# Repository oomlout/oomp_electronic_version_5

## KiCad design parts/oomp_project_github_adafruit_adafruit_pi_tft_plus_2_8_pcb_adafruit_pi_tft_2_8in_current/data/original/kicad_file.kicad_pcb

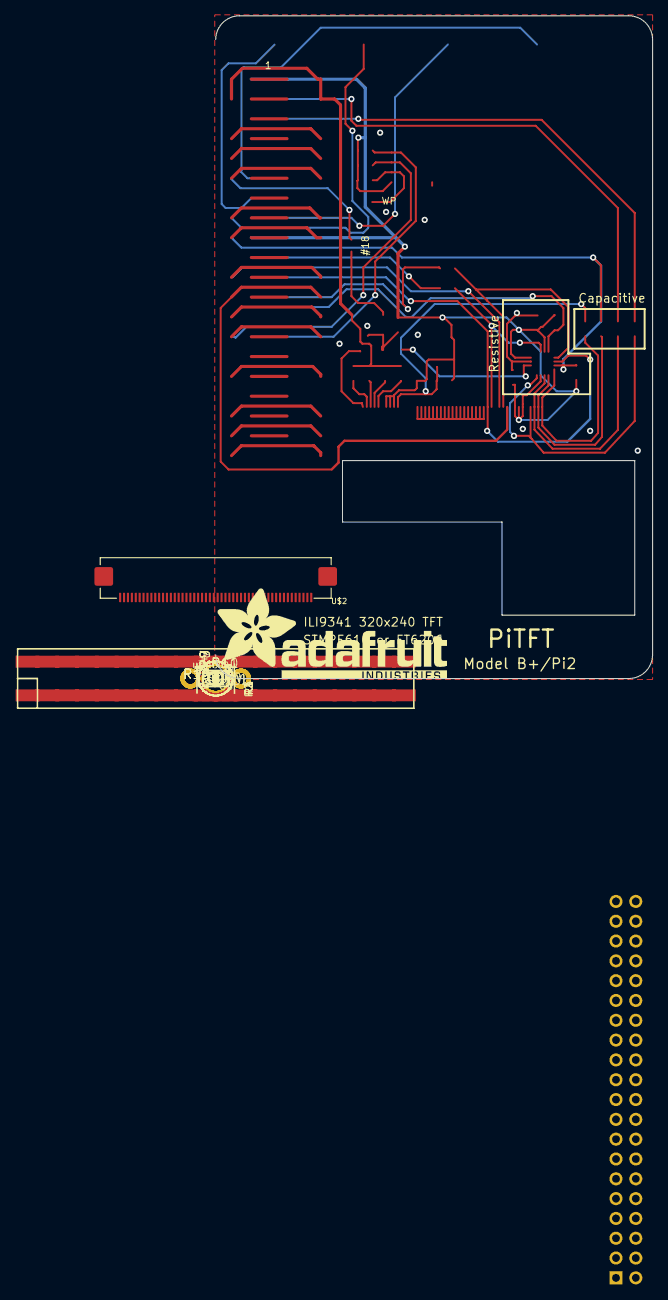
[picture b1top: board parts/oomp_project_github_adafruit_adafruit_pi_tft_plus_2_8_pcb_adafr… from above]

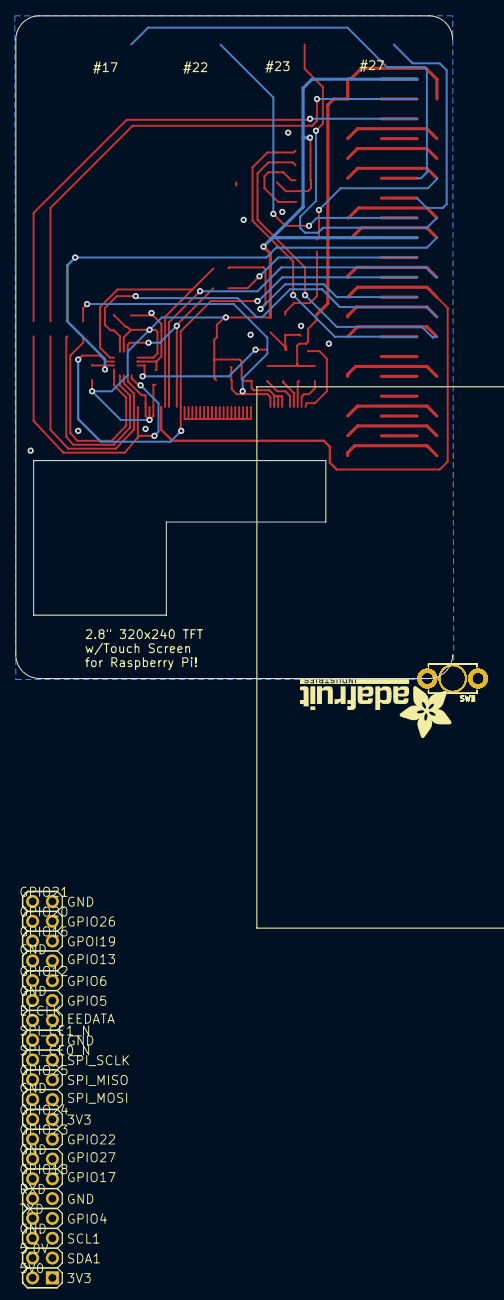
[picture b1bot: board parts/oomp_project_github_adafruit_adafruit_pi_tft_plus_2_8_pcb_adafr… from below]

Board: 16 copper layers, 56.0 x 85.0 mm, 48 parts (7 on the bottom side), 48 nets.

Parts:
C1, C5: 10uF; 0805-NO
C2, C3, C4: 0.1uF; 0805-NO
D1, D2: 1N4148; SOD-323
IC5: APX803; SOT23
JP3: 2X20_SMT_MALE
Q2: BSS138; SOT23-WIDE
R1, R2, R3, R4: 100; 0805-NO
R6, R7: 10K; 0805-NO
R8: DNP; 0805-NO
R9, R12, R13, R14: 3.9K; 0805-NO
R10, R11: 22; 0805-NO
R15, R16, R17, R18: 0; 0805-NO
RPI1: RASPBERRYPI_BPLUS_SHIELD_NODIM
SW1, SW2, SW3, SW4: TACT_PANA-EVQ
U1: CAT24C32; SOIC8_150MIL
U2: STMPE811; QFN16_3MM
U$2: DISP_LCD_240X320_50PIN_2.8IN; TFT_2.83IN_240X320_50PIN
U$3, U$15, U$16, U$17, U$40: MOUNTINGHOLE3.0THIN; MOUNTINGHOLE_3.0_PLATEDTHIN
U$10, U$11, U$18: FIDUCIAL""; FIDUCIAL_1MM
U$12: PCBFEAT-REV-040
U$23: ADAFRUIT_TEXT_20MM
U$42: ADAFRUIT_TEXT_30MM
WPJ0, WPJ1: SOLDERJUMPER_CLOSEDWIRE

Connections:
3.3V: C1.1, C2.1, C3.1, C4.1, IC5.3, JP3.1, JP3.17, R6.2, R7.2, R8.1, R9.2, R12.2, R13.2, R14.2, RPI1.1, RPI1.17, U1.8, U2.6, U2.9, U2.14, U$2.7, U$2.8, U$2.9, U$2.40, U$2.41, U$2.42
+5V: C5.1, JP3.2, JP3.4, R1.1, R2.1, R3.1, R4.1, RPI1.2, RPI1.4
EECLK: JP3.28, R14.1, RPI1.28, U1.6
EEDATA: JP3.27, R13.1, RPI1.27, U1.5
GND: C1.2, C2.2, C3.2, C4.2, C5.2, IC5.1, JP3.6, JP3.9, JP3.14, JP3.20, JP3.25, JP3.30, JP3.34, JP3.39, Q2.2, RPI1.6, RPI1.9, RPI1.14, RPI1.20, RPI1.25, RPI1.30, RPI1.34, RPI1.39, SW1.P$2, SW2.P$2, SW3.P$2, SW4.P$2, U1.1, U1.2, U1.3, U1.4, U2.10, U$2.6, U$2.43, U$2.48, U$2.49, U$2.50, WPJ0.1
GPIO4: JP3.7, RPI1.7
GPIO5: JP3.29, RPI1.29
GPIO6: JP3.31, RPI1.31
GPIO12: JP3.32, RPI1.32
GPIO13: JP3.33, RPI1.33
GPIO16: JP3.36, RPI1.36
GPIO17: JP3.11, RPI1.11, SW3.P$1
GPIO18: JP3.12, RPI1.12, WPJ1.1
GPIO19: JP3.35, RPI1.35
GPIO20: JP3.38, RPI1.38
GPIO21: JP3.40, RPI1.40
GPIO22: JP3.15, RPI1.15, SW1.P$1
GPIO23: JP3.16, RPI1.16, SW4.P$1
GPIO26: JP3.37, RPI1.37
GPIO27: JP3.13, RPI1.13, SW2.P$1
MISO: JP3.21, RPI1.21, U2.3, U$2.33
MOSI: R11.2, U2.7, U$2.34
MOSI_3V: JP3.19, R11.1, RPI1.19
unnamed: Q2.3, U$2.1
unnamed: R1.2, U$2.2
unnamed: R2.2, U$2.3
unnamed: R3.2, U$2.4
unnamed: D1.C, U2.11
unnamed: D2.C, WPJ1.2
unnamed: U$2.15, U$2.16, U$2.17, U$2.18, U$2.19, U$2.20, U$2.21, U$2.22, U$2.23, U$2.24, U$2.25, U$2.26, U$2.27, U$2.28, U$2.29, U$2.30, U$2.31, U$2.32
unnamed: R4.2, U$2.5
unnamed: R12.1, U1.7, WPJ0.2
unnamed: D1.A, D2.A, Q2.1, R9.1
RT_CS_3V: JP3.26, R7.1, RPI1.26, U2.5
RT_INT: JP3.18, R8.2, R18.2, RPI1.18, U2.2
RXD: JP3.10, RPI1.10
SCL: JP3.5, R17.2, RPI1.5
SCLK: R10.2, U2.4, U$2.37
SCLK_3V: JP3.23, R10.1, RPI1.23
SDA: JP3.3, R16.2, RPI1.3
TFT_CS_3V: JP3.24, RPI1.24, U$2.38
TFT_DC_3V: JP3.22, RPI1.22, U$2.36
TFT_RST: IC5.2, R6.1, R15.2, U$2.10
TXD: JP3.8, RPI1.8
XL_CTPIRQ: R18.1, U2.16, U$2.46
XR_CTPSCL: R17.1, U2.13, U$2.44
YD_CTPSDA: R16.1, U2.15, U$2.45
YU_CTPRST: R15.1, U2.1, U$2.47

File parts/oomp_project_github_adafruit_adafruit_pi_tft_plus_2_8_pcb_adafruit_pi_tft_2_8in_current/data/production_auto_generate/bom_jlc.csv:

Comment,Designator,Footprint,LCSC Part #
,JP3,Adafruit PiTFT+ 2.8in-import-fps:2X20_SMT_MALE,
,U$23,Adafruit PiTFT+ 2.8in-import-fps:ADAFRUIT_TEXT_20MM,
,U$42,Adafruit PiTFT+ 2.8in-import-fps:ADAFRUIT_TEXT_30MM,
,U$12,Adafruit PiTFT+ 2.8in-import-fps:PCBFEAT-REV-040,
,"WPJ0,WPJ1",Adafruit PiTFT+ 2.8in-import-fps:SOLDERJUMPER_CLOSEDWIRE,
0,"R15,R16,R17,R18",Adafruit PiTFT+ 2.8in-import-fps:0805-NO,C2907288
0.1uF,"C2,C3,C4",Adafruit PiTFT+ 2.8in-import-fps:0805-NO,
100,"R1,R2,R3,R4",Adafruit PiTFT+ 2.8in-import-fps:0805-NO,C17408
10K,"R6,R7",Adafruit PiTFT+ 2.8in-import-fps:0805-NO,C17414
10uF,"C1,C5",Adafruit PiTFT+ 2.8in-import-fps:0805-NO,
1N4148,"D1,D2",Adafruit PiTFT+ 2.8in-import-fps:SOD-323,
22,"R10,R11",Adafruit PiTFT+ 2.8in-import-fps:0805-NO,C2907310
3.9K,"R9,R12,R13,R14",Adafruit PiTFT+ 2.8in-import-fps:0805-NO,C2907252
APX803,IC5,Adafruit PiTFT+ 2.8in-import-fps:SOT23,
BSS138,Q2,Adafruit PiTFT+ 2.8in-import-fps:SOT23-WIDE,C52895
CAT24C32,U1,Adafruit PiTFT+ 2.8in-import-fps:SOIC8_150MIL,
DISP_LCD_240X320_50PIN_2.8IN,U$2,Adafruit PiTFT+ 2.8in-import-fps:TFT_2.83IN_240X320_50PIN,
DNP,R8,Adafruit PiTFT+ 2.8in-import-fps:0805-NO,
"FIDUCIAL""""","U$10,U$11,U$18",Adafruit PiTFT+ 2.8in-import-fps:FIDUCIAL_1MM,
RASPBERRYPI_BPLUS_SHIELD_NODIM,RPI1,Adafruit PiTFT+ 2.8in-import-fps:RASPBERRYPI_BPLUS_SHIELD_NODIM,
STMPE811,U2,Adafruit PiTFT+ 2.8in-import-fps:QFN16_3MM,

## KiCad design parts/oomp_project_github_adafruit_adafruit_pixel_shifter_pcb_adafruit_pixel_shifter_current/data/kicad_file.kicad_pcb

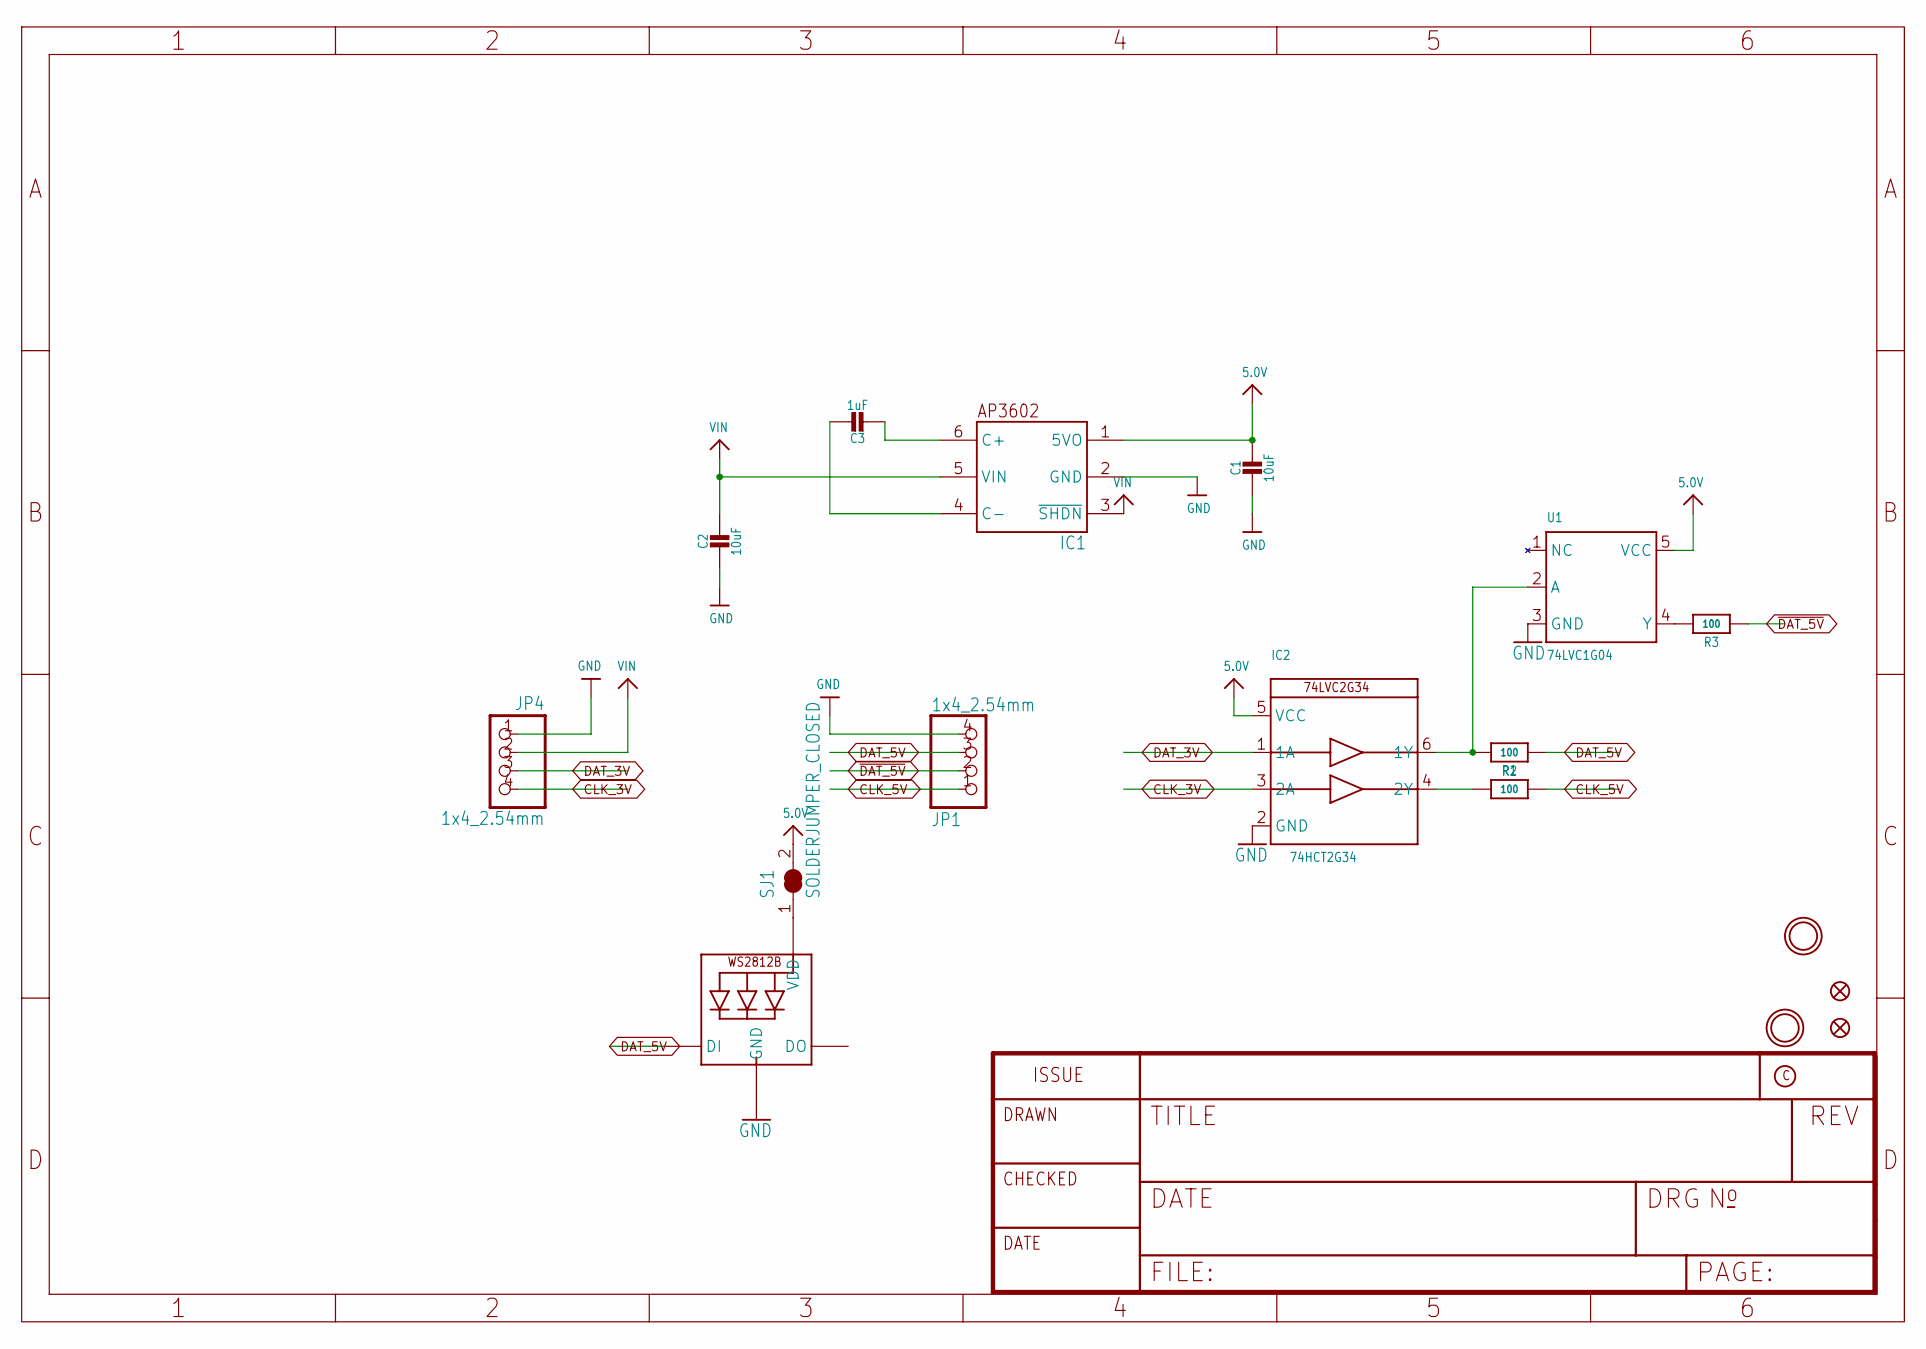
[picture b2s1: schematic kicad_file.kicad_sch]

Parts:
C1, C2: 10uF; 0805-NO
C3: 1uF; 0603-NO_WIDE
FID1, FID2: FIDUCIAL_0.5MM
IC1: AP3602; SOT23-6
IC2: 74HCT2G34; SC70-6L
JP1, JP4: 1x4_2.54mm; 1X04_2.54MMTERMINAL
LED1: WS2812B_SK6805_1515; SK6805_1515; LCSC C2890035
R1, R2, R3: 100; _0402NO
SJ1: SOLDERJUMPER_CLOSED; SOLDERJUMPER_CLOSEDWIRE
U1: 74LVC1G04; SC70-5
U$6, U$9: MOUNTINGHOLE2.5; MOUNTINGHOLE_2.5_PLATED

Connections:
5.0V: C1.1, IC1.1 (5VO), IC2.5 (VCC), SJ1.2, U1.5 (VCC)
CLK_3V: IC2.3 (2A), JP4.4
CLK_5V: JP1.1, R1.2
DAT_3V: IC2.1 (1A), JP4.3
DAT_5V: JP1.3, LED1.1 (DI), R2.2
GND: C1.2, C2.2, IC1.2 (GND), IC2.2 (GND), JP1.4, JP4.1, LED1.4 (GND), U1.3 (GND)
unnamed: C3.2, IC1.6 (C+)
unnamed: C3.1, IC1.4 (C-)
unnamed: IC2.4 (2Y), R1.1
unnamed: R3.1, U1.4 (Y)
unnamed: IC2.6 (1Y), R2.1, U1.2 (A)
unnamed: LED1.2 (VDD), SJ1.1
VIN: C2.1, IC1.3 (~SHDN), IC1.5 (VIN), JP4.2
~DAT_5V: JP1.2, R3.2

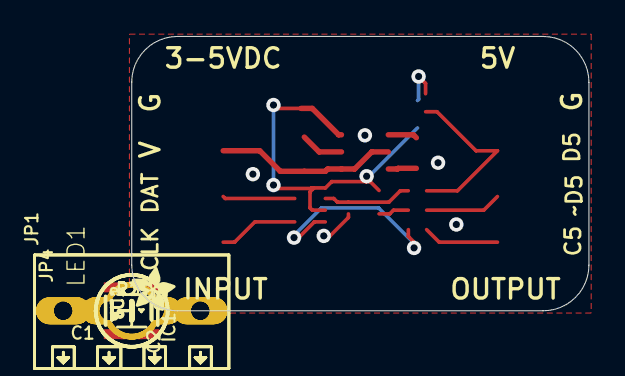
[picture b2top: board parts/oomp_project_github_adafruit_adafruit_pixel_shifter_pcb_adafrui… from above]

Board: 2 copper layers, 25.4 x 15.2 mm, 18 parts (1 on the bottom side), 14 nets.

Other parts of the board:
U$11: ADAFRUIT_2.5MM

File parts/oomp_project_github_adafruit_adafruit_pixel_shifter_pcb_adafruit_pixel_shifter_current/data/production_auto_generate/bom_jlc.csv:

Comment,Designator,Footprint,LCSC Part #
,U$11,Adafruit Pixel Shifter-import-fps:ADAFRUIT_2.5MM,
100,"R1,R2,R3",Adafruit Pixel Shifter-import-fps:_0402NO,C2906860
10uF,"C1,C2",Adafruit Pixel Shifter-import-fps:0805-NO,
1uF,C3,Adafruit Pixel Shifter-import-fps:0603-NO_WIDE,C5673
1x4_2.54mm,"JP1,JP4",Adafruit Pixel Shifter-import-fps:1X04_2.54MMTERMINAL,C42431795
74HCT2G34,IC2,Adafruit Pixel Shifter-import-fps:SC70-6L,
74LVC1G04,U1,Adafruit Pixel Shifter-import-fps:SC70-5,
AP3602,IC1,Adafruit Pixel Shifter-import-fps:SOT23-6,
WS2812B_SK6805_1515,LED1,Adafruit Pixel Shifter-import-fps:SK6805_1515,

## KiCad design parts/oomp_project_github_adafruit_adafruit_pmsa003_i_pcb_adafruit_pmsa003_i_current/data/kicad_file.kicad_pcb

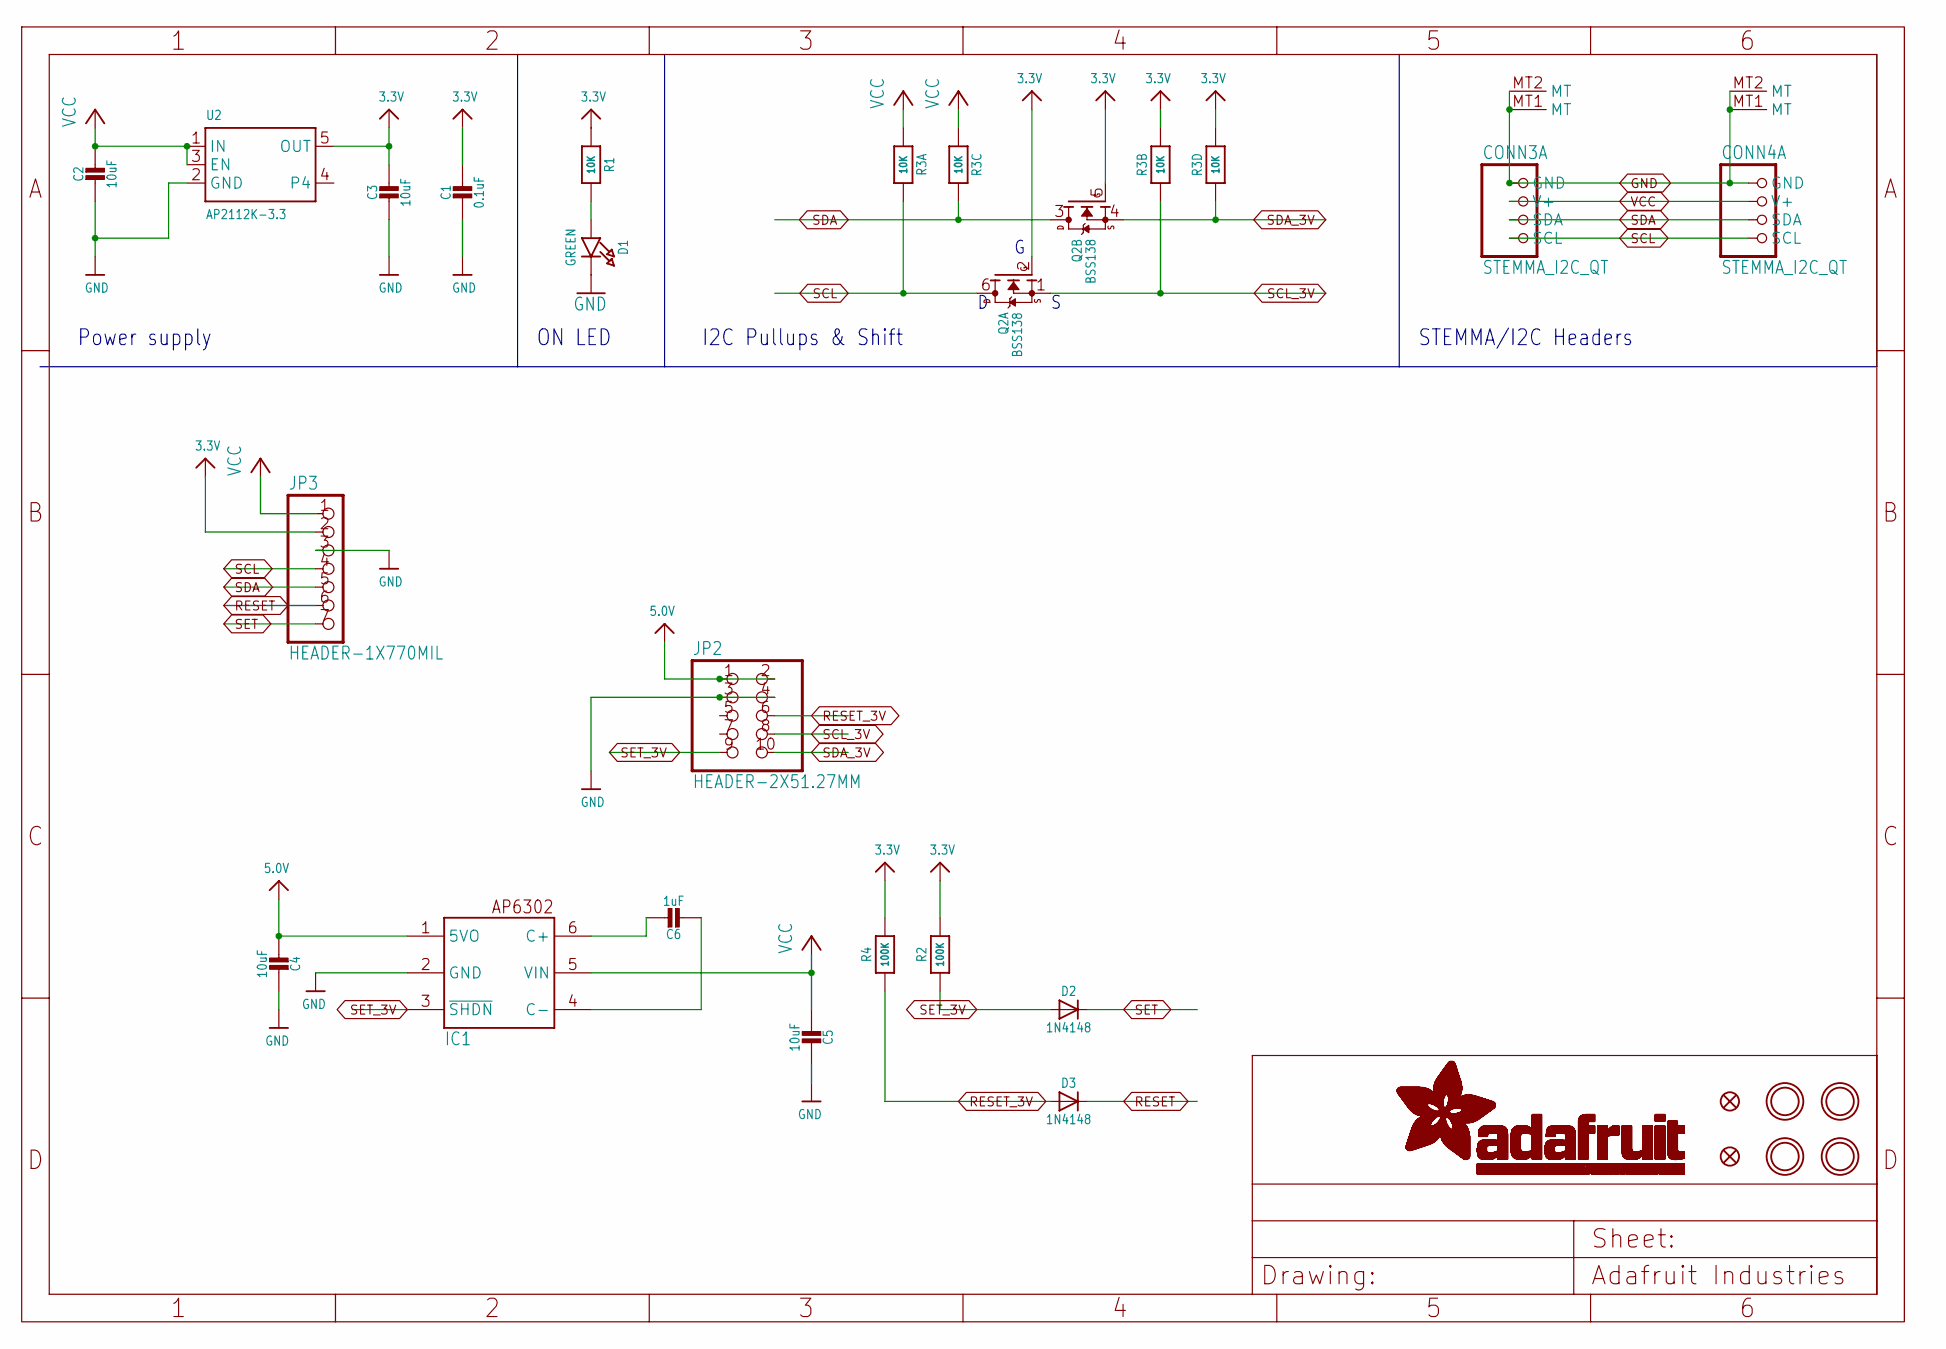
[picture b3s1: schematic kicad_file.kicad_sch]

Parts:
C1: 0.1uF; 0603-NO
C2, C3, C4: 10uF; 0805-NO
C5: 10uF; 0805_10MGAP
C6: 1uF; 0805-NO
CONN3, CONN4: STEMMA_I2C_QT; JST_SH4
D1: GREEN; CHIPLED_0603_NOOUTLINE
D2, D3: 1N4148; SOD-323
FID3, FID4: FIDUCIAL_1MM
IC1: AP3602/RT9361; SOT23-6
JP2: HEADER-2X51.27MM; 2X05_1.27MM_SMT
JP3: HEADER-1X770MIL; 1X07_ROUND_70
Q2: BSS138; SOT363
R1: 10K; 0603-NO
R2, R4: 100K; 0603-NO
R3: 10K; RESPACK_4X0603
U2: AP2112K-3.3; SOT23-5
U$1, U$17, U$19, U$21: MOUNTINGHOLE2.5; MOUNTINGHOLE_2.5_PLATED

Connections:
3.3V: C1.1, C3.1, JP3.2, Q2.2 (G), Q2.5 (G), R1.1, R2.1, R3.2 (1), R3.4 (1), R4.1, U2.5 (OUT)
5.0V: C4.1, IC1.1 (5VO), JP2.1, JP2.2
GND: C1.2, C2.2, C3.2, C4.2, C5.2, CONN3.1 (GND), CONN3.MT1 (MT), CONN3.MT2 (MT), CONN4.1 (GND), CONN4.MT1 (MT), CONN4.MT2 (MT), D1.C, IC1.2 (GND), JP2.3, JP2.4, JP3.3, U2.2 (GND)
unnamed: D1.A, R1.2
unnamed: C6.2, IC1.6 (C+)
unnamed: C6.1, IC1.4 (C-)
RESET: D3.C, JP3.6
RESET_3V: D3.A, JP2.6, R4.2
SCL: CONN3.4 (SCL), CONN4.4 (SCL), JP3.4, Q2.6 (D), R3.8 (2)
SCL_3V: JP2.8, Q2.1 (S), R3.7 (2)
SDA: CONN3.3 (SDA), CONN4.3 (SDA), JP3.5, Q2.3 (D), R3.6 (2)
SDA_3V: JP2.10, Q2.4 (S), R3.5 (2)
SET: D2.C, JP3.7
SET_3V: D2.A, IC1.3 (~SHDN), JP2.9, R2.2
VCC: C2.1, C5.1, CONN3.2 (V+), CONN4.2 (V+), IC1.5 (VIN), JP3.1, R3.1, R3.3 (1), U2.1 (IN), U2.3 (EN)

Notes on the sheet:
I2C Pullups & Shift
STEMMA/I2C Headers
ON LED
Power supply

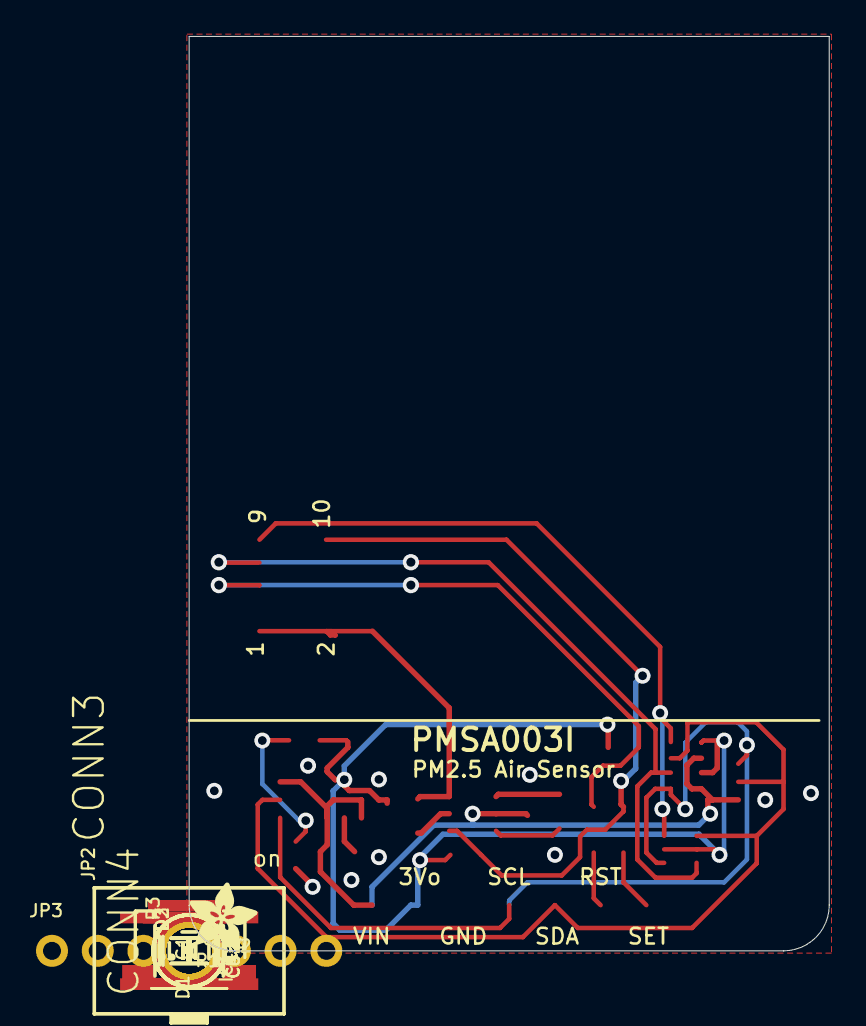
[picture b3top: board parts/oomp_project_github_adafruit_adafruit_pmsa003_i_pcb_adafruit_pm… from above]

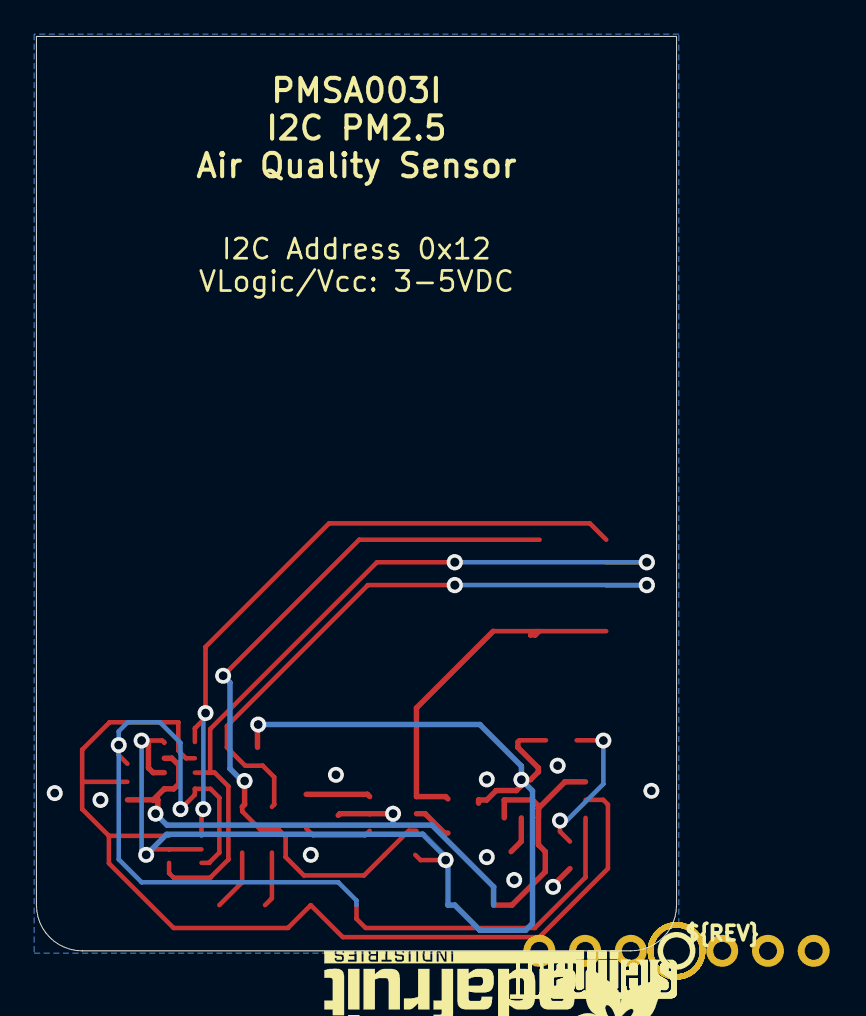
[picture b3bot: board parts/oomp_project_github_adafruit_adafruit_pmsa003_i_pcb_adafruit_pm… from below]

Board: 2 copper layers, 35.6 x 50.8 mm, 31 parts (4 on the bottom side), 15 nets.

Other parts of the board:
U$22: ADAFRUIT_3.5MM
U$25: PCBFEAT-REV-040
U$28: ADAFRUIT_TEXT_20MM
U$30, U$31: STEMMAQT

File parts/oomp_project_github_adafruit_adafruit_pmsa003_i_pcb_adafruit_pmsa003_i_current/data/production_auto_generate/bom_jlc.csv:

Comment,Designator,Footprint,LCSC Part #
,JP3,Adafruit PMSA003I-import-fps:1X07_ROUND_70,C7501585
,JP2,Adafruit PMSA003I-import-fps:2X05_1.27MM_SMT,
,U$22,Adafruit PMSA003I-import-fps:ADAFRUIT_3.5MM,
,U$28,Adafruit PMSA003I-import-fps:ADAFRUIT_TEXT_20MM,
,U$25,Adafruit PMSA003I-import-fps:PCBFEAT-REV-040,
,"U$30,U$31",Adafruit PMSA003I-import-fps:STEMMAQT,
0.1uF,C1,Adafruit PMSA003I-import-fps:0603-NO,C14663
100K,"R2,R4",Adafruit PMSA003I-import-fps:0603-NO,C25803
10K,R1,Adafruit PMSA003I-import-fps:0603-NO,C98220
10K,R3,Adafruit PMSA003I-import-fps:RESPACK_4X0603,C98220
10uF,"C2,C3,C4",Adafruit PMSA003I-import-fps:0805-NO,
10uF,C5,Adafruit PMSA003I-import-fps:0805_10MGAP,
1N4148,"D2,D3",Adafruit PMSA003I-import-fps:SOD-323,
1uF,C6,Adafruit PMSA003I-import-fps:0805-NO,
AP2112K-3.3,U2,Adafruit PMSA003I-import-fps:SOT23-5,
AP3602/RT9361,IC1,Adafruit PMSA003I-import-fps:SOT23-6,
BSS138,Q2,Adafruit PMSA003I-import-fps:SOT363,
GREEN,D1,Adafruit PMSA003I-import-fps:CHIPLED_0603_NOOUTLINE,
STEMMA_I2C_QT,"CONN3,CONN4",Adafruit PMSA003I-import-fps:JST_SH4,C160404

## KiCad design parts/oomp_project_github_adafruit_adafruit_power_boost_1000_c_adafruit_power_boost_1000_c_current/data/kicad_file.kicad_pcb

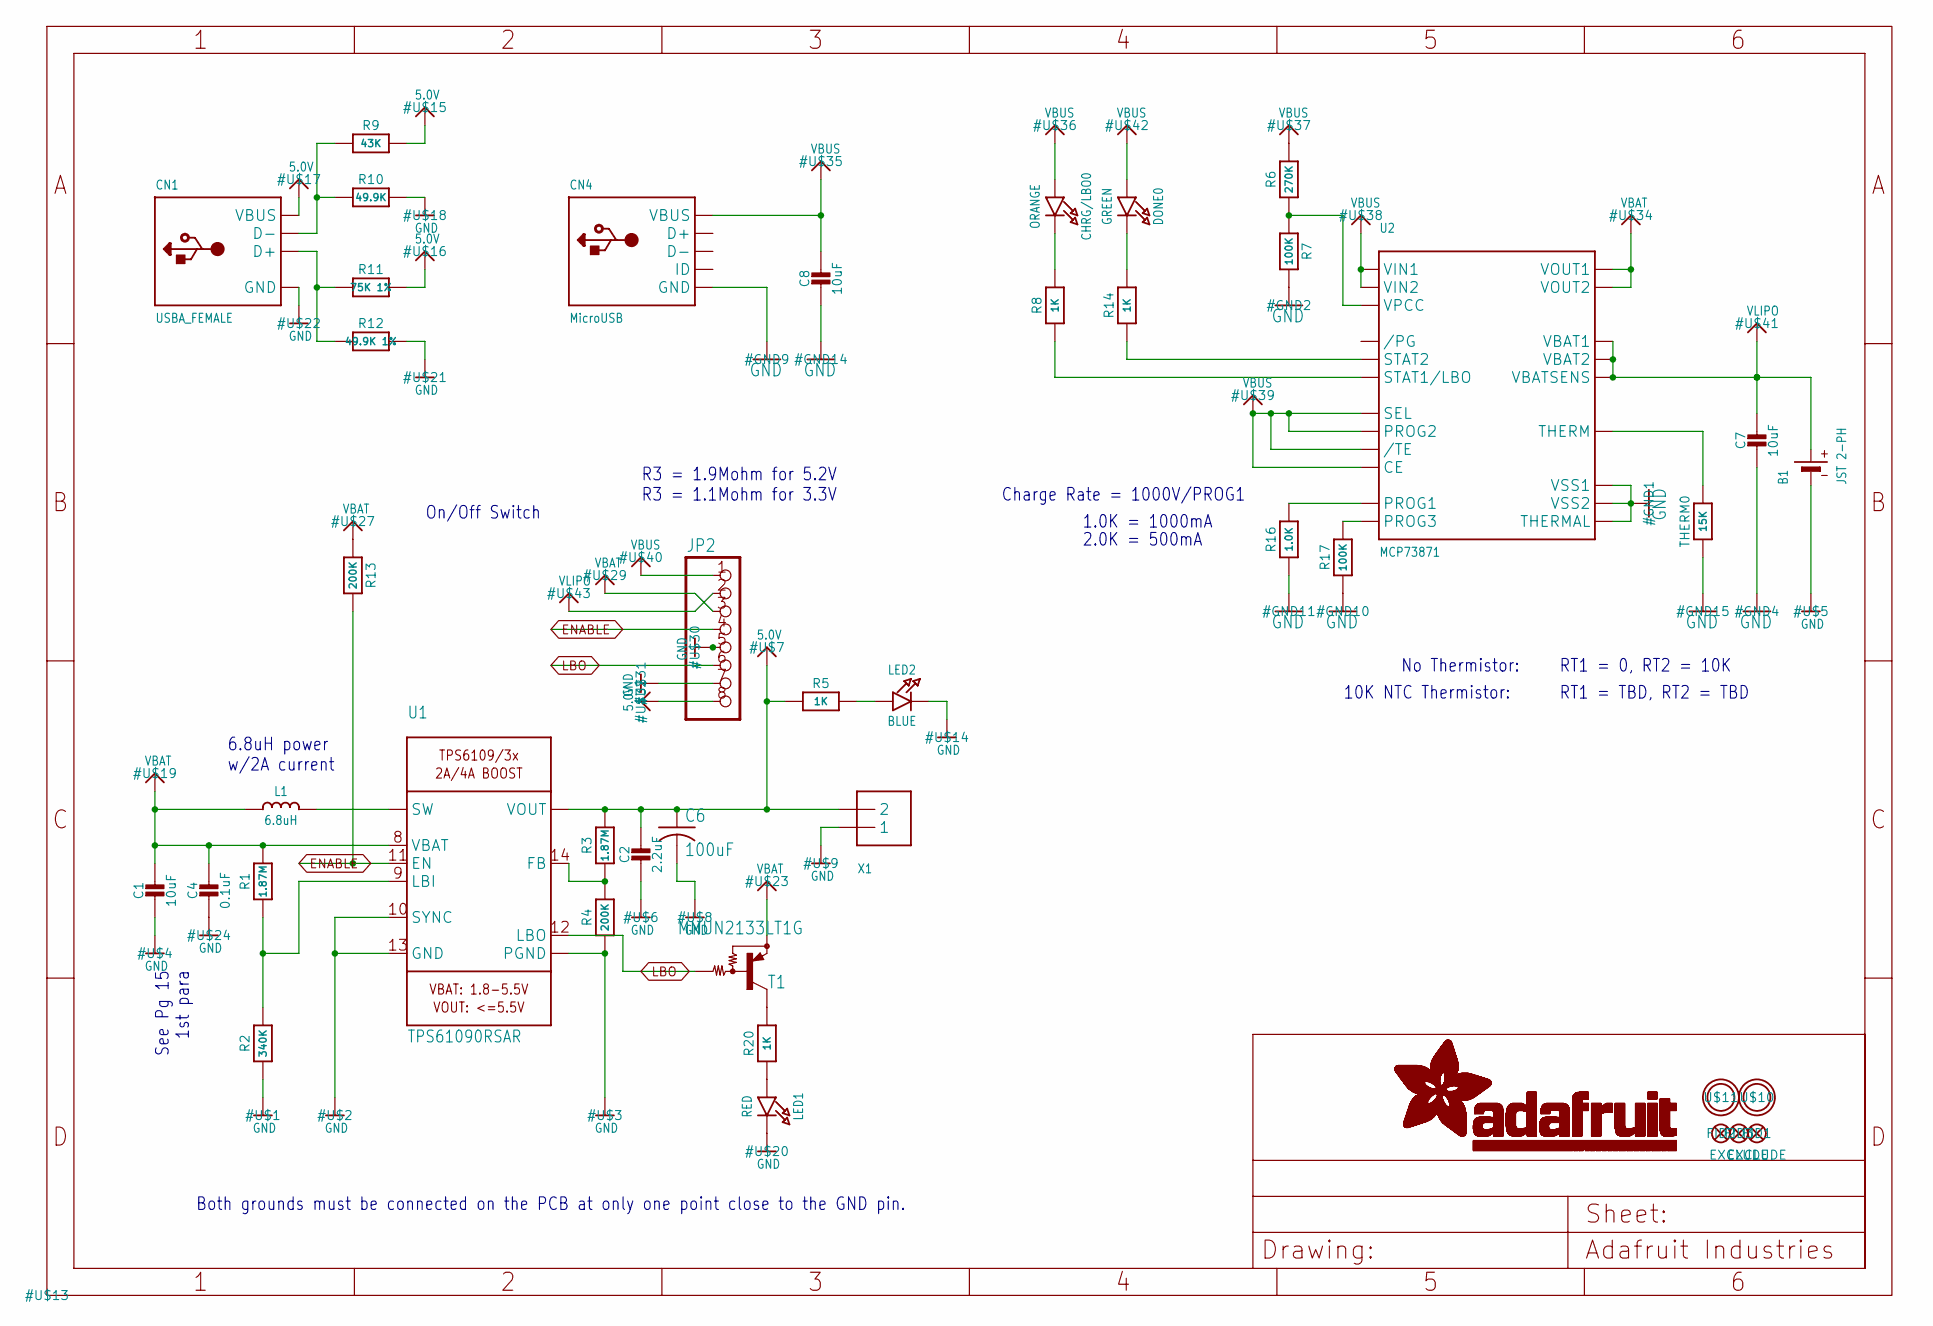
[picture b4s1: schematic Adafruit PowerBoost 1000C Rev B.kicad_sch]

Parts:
B1: JST 2-PH; JSTPH2
C1, C7, C8: 10uF; 0805-NO
C2: 2.2uF; 0805-NO
C4: 0.1uF; 0805_10MGAP
C6: 100uF; C1210
CHRG/LBO0: ORANGE; CHIPLED_0805_NOOUTLINE
CN1: USBA_FEMALE; USB_HOST-PTH
CN4: MicroUSB; 4UCONN_20329
DONE0: GREEN; CHIPLED_0805_NOOUTLINE
FID1, FID2, FID3: FIDUCIAL""; FIDUCIAL_1MM
JP2: HEADER-1X8ROUND; 1X08_ROUND
L1: 6.8uH; INDUCTOR_5X5MM_TDK_VLC5045
LED1: RED; CHIPLED_0805_NOOUTLINE
LED2: BLUE; CHIPLED_0805_NOOUTLINE
R1: 1.87M; _0805MP
R2: 340K; _0805MP
R3: 1.87M; 0805-NO
R4, R13: 200K; 0805-NO
R5, R8, R14, R20: 1K; 0805-NO
R6: 270K; 0805-NO
R7, R17: 100K; 0805-NO
R9: 43K; 0805-NO
R10: 49.9K; 0805-NO
R11: 75K 1%; 0805-NO
R12: 49.9K 1%; 0805-NO
R16: 1.0K; 0805-NO
T1: MMUN2133LT1G; SC59-BEC
THERM0: 15K; 0805-NO
U1: TPS61090RSAR; PVQFN-16
U2: MCP73871; QFN20_4MM
U$10, U$11: MOUNTINGHOLE2.5; MOUNTINGHOLE_2.5_PLATED
X1: TERMBLOCK_1X2; TERMBLOCK_1X2-3.5MM

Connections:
5.0V: C2.1, C6.1, CN1.VBUS, JP2.8, R3.2, R5.1, R9.2, R11.2, U1.1 (VOUT), U1.15 (VOUT), U1.16 (VOUT), X1.2
D+: CN1.D+, R11.1, R12.1
D-: CN1.D-, R9.1, R10.1
ENABLE: JP2.4, R13.2, U1.11 (EN)
GND: B1.1 (-), C1.2, C2.2, C4.2, C6.2, C7.2, C8.2, CN1.GND, CN4.BASE@1 (GND), CN4.BASE@2 (GND), CN4.GND, CN4.SPRT@1 (GND), CN4.SPRT@2 (GND), CN4.SPRT@3 (GND), CN4.SPRT@4 (GND), JP2.5, JP2.7, LED1.C, LED2.C, R2.1, R4.1, R7.2, R10.2, R12.2, R16.1, R17.1, THERM0.1, U1.5 (PGND), U1.6 (PGND), U1.7 (PGND), U1.10 (SYNC), U1.13 (GND), U1.P$18 (PGND), U1.P$19 (PGND), U1.P$20 (PGND), U1.P$21 (PGND), U1.P$22 (PGND), U1.THERMAL (PGND), U2.P$10 (VSS1), U2.P$11 (VSS2), U2.P$21 (THERMAL), X1.1
LBO: JP2.6, T1.B, U1.12 (LBO)
unnamed: L1.P$2 (2), U1.3 (SW), U1.4 (SW)
unnamed: LED1.A, R20.1
unnamed: R1.1, R2.2, U1.9 (LBI)
unnamed: LED2.A, R5.2
unnamed: R3.1, R4.2, U1.14 (FB)
unnamed: R20.2, T1.C
unnamed: R6.1, R7.1, U2.P$2 (VPCC)
unnamed: DONE0.C, R14.2
unnamed: R14.1, U2.P$7 (STAT2)
unnamed: THERM0.2, U2.P$5 (THERM)
unnamed: R8.1, U2.P$8 (STAT1/LBO)
unnamed: CHRG/LBO0.C, R8.2
unnamed: R17.2, U2.P$12 (PROG3)
unnamed: R16.2, U2.P$13 (PROG1)
VBAT: C1.1, C4.1, JP2.3, L1.P$1 (1), R1.2, R13.1, T1.E, U1.8 (VBAT), U2.P$1 (VOUT1), U2.P$20 (VOUT2)
VBUS: C8.1, CHRG/LBO0.A, CN4.VBUS, DONE0.A, JP2.1, R6.2, U2.P$3 (SEL), U2.P$4 (PROG2), U2.P$9 (/TE), U2.P$17 (CE), U2.P$18 (VIN1), U2.P$19 (VIN2)
VLIPO: B1.2 (+), C7.1, JP2.2, U2.P$14 (VBAT1), U2.P$15 (VBAT2), U2.P$16 (VBATSENS)

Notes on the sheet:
Both grounds must be connected on the PCB at only one point close to the GND pin.
No Thermistor:
RT1 = 0, RT2 = 10K
RT1 = TBD, RT2 = TBD
R3 = 1.9Mohm for 5.2V R3 = 1.1Mohm for 3.3V
1.0K = 1000mA
Charge Rate = 1000V/PROG1
10K NTC Thermistor:
6.8uH power w/2A current
2.0K = 500mA
See Pg 15 1st para
On/Off Switch

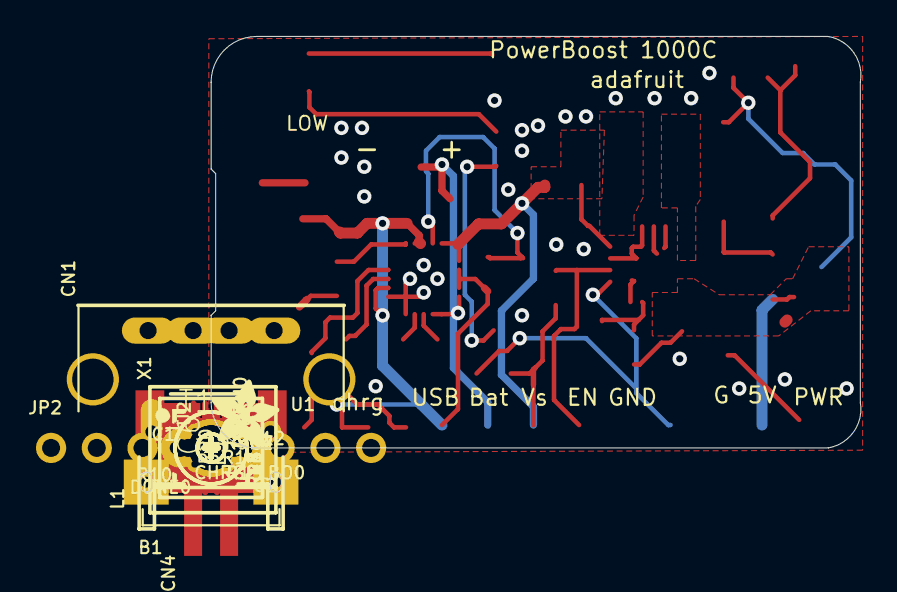
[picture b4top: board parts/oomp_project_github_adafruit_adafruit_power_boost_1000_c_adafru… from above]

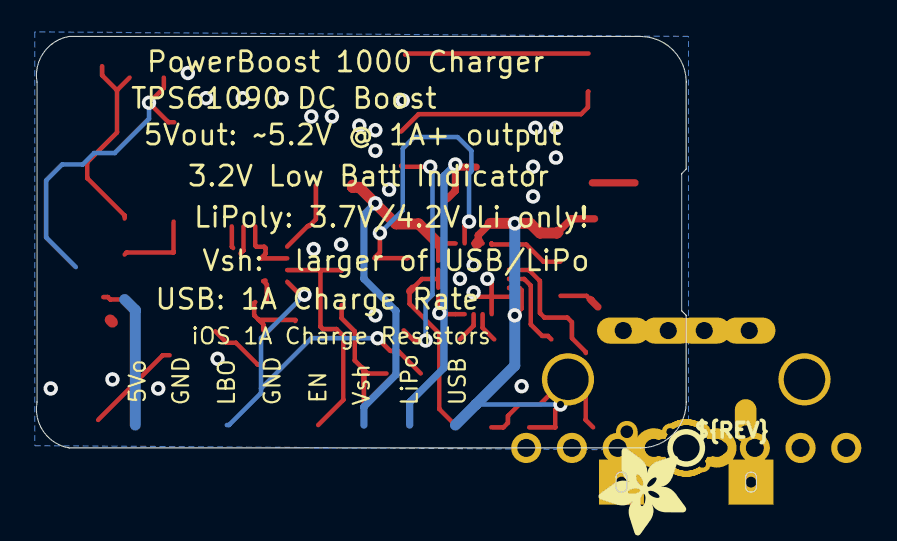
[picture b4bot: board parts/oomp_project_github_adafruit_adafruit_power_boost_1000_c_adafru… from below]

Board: 2 copper layers, 36.1 x 22.9 mm, 47 parts (2 on the bottom side), 23 nets.

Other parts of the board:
U$12: PCBFEAT-REV-040
U$25: SYMBOL_PLUS
U$26: SYMBOL_MINUS
U$28: ADAFRUIT_5MM
U$45: ADAFRUIT_3.5MM

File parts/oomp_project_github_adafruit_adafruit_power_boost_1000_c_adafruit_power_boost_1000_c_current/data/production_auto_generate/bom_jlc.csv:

Comment,Designator,Footprint,LCSC Part #
,JP2,Adafruit PowerBoost 1000C Rev B-import-fps:1X08_ROUND,C492421
,U$45,Adafruit PowerBoost 1000C Rev B-import-fps:ADAFRUIT_3.5MM,
,U$28,Adafruit PowerBoost 1000C Rev B-import-fps:ADAFRUIT_5MM,
,U$12,Adafruit PowerBoost 1000C Rev B-import-fps:PCBFEAT-REV-040,
,U$26,Adafruit PowerBoost 1000C Rev B-import-fps:SYMBOL_MINUS,
,U$25,Adafruit PowerBoost 1000C Rev B-import-fps:SYMBOL_PLUS,
,X1,Adafruit PowerBoost 1000C Rev B-import-fps:TERMBLOCK_1X2-3.5MM,
0.1uF,C4,Adafruit PowerBoost 1000C Rev B-import-fps:0805_10MGAP,
1.0K,R16,Adafruit PowerBoost 1000C Rev B-import-fps:0805-NO,C17513
1.87M,R3,Adafruit PowerBoost 1000C Rev B-import-fps:0805-NO,
1.87M,R1,Adafruit PowerBoost 1000C Rev B-import-fps:_0805MP,
100K,"R7,R17",Adafruit PowerBoost 1000C Rev B-import-fps:0805-NO,C149504
100uF,C6,Adafruit PowerBoost 1000C Rev B-import-fps:C1210,
10uF,"C1,C7,C8",Adafruit PowerBoost 1000C Rev B-import-fps:0805-NO,
15K,THERM0,Adafruit PowerBoost 1000C Rev B-import-fps:0805-NO,
1K,"R5,R8,R14,R20",Adafruit PowerBoost 1000C Rev B-import-fps:0805-NO,C17513
2.2uF,C2,Adafruit PowerBoost 1000C Rev B-import-fps:0805-NO,
200K,"R4,R13",Adafruit PowerBoost 1000C Rev B-import-fps:0805-NO,
270K,R6,Adafruit PowerBoost 1000C Rev B-import-fps:0805-NO,C2930189
340K,R2,Adafruit PowerBoost 1000C Rev B-import-fps:_0805MP,
43K,R9,Adafruit PowerBoost 1000C Rev B-import-fps:0805-NO,
49.9K,R10,Adafruit PowerBoost 1000C Rev B-import-fps:0805-NO,
49.9K 1%,R12,Adafruit PowerBoost 1000C Rev B-import-fps:0805-NO,
6.8uH,L1,Adafruit PowerBoost 1000C Rev B-import-fps:INDUCTOR_5X5MM_TDK_VLC5045,
75K 1%,R11,Adafruit PowerBoost 1000C Rev B-import-fps:0805-NO,C17819
BLUE,LED2,Adafruit PowerBoost 1000C Rev B-import-fps:CHIPLED_0805_NOOUTLINE,
GREEN,DONE0,Adafruit PowerBoost 1000C Rev B-import-fps:CHIPLED_0805_NOOUTLINE,
JST 2-PH,B1,Adafruit PowerBoost 1000C Rev B-import-fps:JSTPH2,
MCP73871,U2,Adafruit PowerBoost 1000C Rev B-import-fps:QFN20_4MM,
MicroUSB,CN4,Adafruit PowerBoost 1000C Rev B-import-fps:4UCONN_20329,
MMUN2133LT1G,T1,Adafruit PowerBoost 1000C Rev B-import-fps:SC59-BEC,
ORANGE,CHRG/LBO0,Adafruit PowerBoost 1000C Rev B-import-fps:CHIPLED_0805_NOOUTLINE,
RED,LED1,Adafruit PowerBoost 1000C Rev B-import-fps:CHIPLED_0805_NOOUTLINE,
TPS61090RSAR,U1,Adafruit PowerBoost 1000C Rev B-import-fps:PVQFN-16,
USBA_FEMALE,CN1,Adafruit PowerBoost 1000C Rev B-import-fps:USB_HOST-PTH,
